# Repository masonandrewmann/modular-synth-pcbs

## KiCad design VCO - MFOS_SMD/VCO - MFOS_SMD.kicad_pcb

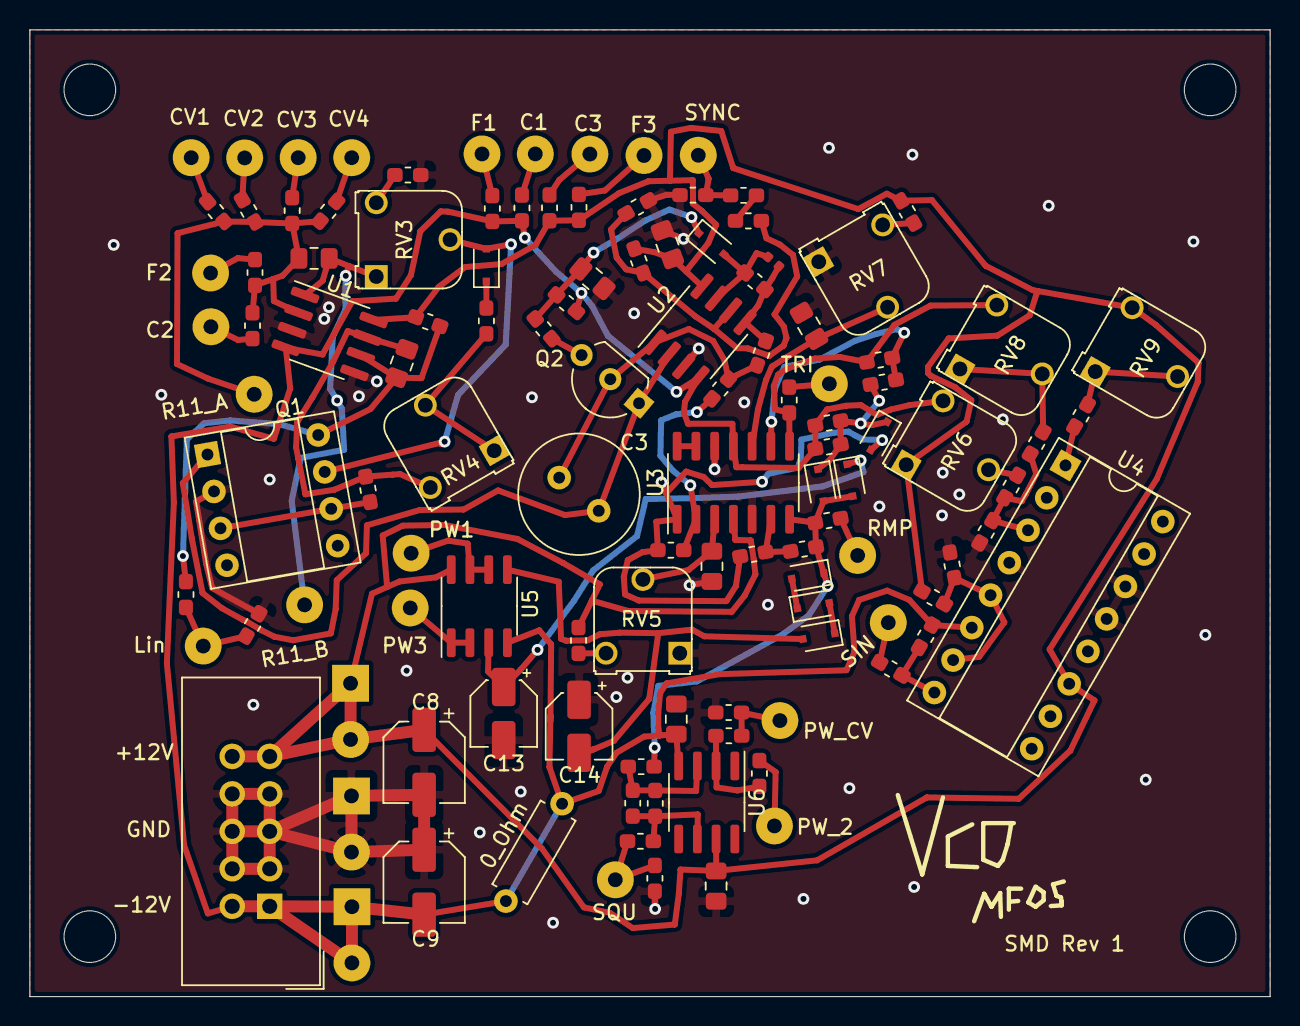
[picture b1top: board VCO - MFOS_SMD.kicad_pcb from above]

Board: 2 copper layers, 84.1 x 65.5 mm, 117 parts (0 on the bottom side), 66 nets.

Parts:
0_Ohm: R_Axial_DIN0207_L6.3mm_D2.5mm_P7.62mm_Horizontal
C1, C2, C5: 100pF; C_0805_2012Metric_Pad1.15x1.40mm_HandSolder
C3: 0.005uF; C_Radial_D8.0mm_H7.0mm_P3.50mm
C4: 0.001uF; C_0603_1608Metric_Pad1.05x0.95mm_HandSolder
C6: 4.7pF; C_0402_1005Metric
C7, C10, C11, C16, C17: 0.1uF; C_0805_2012Metric_Pad1.15x1.40mm_HandSolder
C8, C9: 10uF; CP_Elec_5x5.4
C12: 0.002uF; C_0603_1608Metric_Pad1.05x0.95mm_HandSolder
C13, C14: 1uF; CP_Elec_4x5.4
C15: 10pF; C_0603_1608Metric_Pad1.05x0.95mm_HandSolder
D1, D2, D3, D4, D5, D6, D7, D8: D; D_SOD-323F
J1: CV1; SolderWirePad_1x01_Drill1mm
J2: CV2; SolderWirePad_1x01_Drill1mm
J3: CV3; SolderWirePad_1x01_Drill1mm
J4: CV4; SolderWirePad_1x01_Drill1mm
J5: LIN; SolderWirePad_1x01_Drill1mm
J6: SYNC; SolderWirePad_1x01_Drill1mm
J7: RMP; SolderWirePad_1x01_Drill1mm
J8: TRI; SolderWirePad_1x01_Drill1mm
J9: SIN; SolderWirePad_1x01_Drill1mm
J10: PWM_CV; SolderWirePad_1x01_Drill1mm
J11: SQU; SolderWirePad_1x01_Drill1mm
J12: RV1P2; SolderWirePad_1x01_Drill1mm
J13: RV2P2; SolderWirePad_1x01_Drill1mm
J14: RV1P1; SolderWirePad_1x01_Drill1mm
J15: RV2P1; SolderWirePad_1x01_Drill1mm
J16: RV2P3; SolderWirePad_1x01_Drill1mm
J17: RV1P3; SolderWirePad_1x01_Drill1mm
J18: RV10P3; SolderWirePad_1x01_Drill1mm
J19: RV10P1; SolderWirePad_1x01_Drill1mm
J20: RV10P2; SolderWirePad_1x01_Drill1mm
J21: GND_CONN; SolderWirePad_1x02_P3.81mm_Drill1mm
J22: +12V_CONN; SolderWirePad_1x02_P3.81mm_Drill1mm
J23: -12V_CONN; SolderWirePad_1x02_P3.81mm_Drill1mm
J24: R11_inv; SolderWirePad_1x01_Drill1mm
J25: R11_out; SolderWirePad_1x01_Drill1mm
J26: Conn_01x10_Female; IDC-Header_2x05_P2.54mm_Vertical
Q1: SSM2210; DIP-8_W7.62mm_Socket
Q2: Q_PJFET_DSG; TO-92L_Inline_Wide
R1, R9: 200k; R_0603_1608Metric_Pad1.05x0.95mm_HandSolder
R2: 10k; R_0603_1608Metric_Pad1.05x0.95mm_HandSolder
R3, R14, R17, R25, R40: 1M; R_0603_1608Metric_Pad1.05x0.95mm_HandSolder
R4, R5, R6, R7, R8: 100k; R_0603_1608Metric_Pad1.05x0.95mm_HandSolder
R10: 47k; R_0603_1608Metric_Pad1.05x0.95mm_HandSolder
R12: 475; R_0603_1608Metric_Pad1.05x0.95mm_HandSolder
R13, R18, R20, R27, R38, R45, R46: 100K; R_0603_1608Metric_Pad1.05x0.95mm_HandSolder
R15, R44, R50: 4.7K; R_0603_1608Metric_Pad1.05x0.95mm_HandSolder
R16, R21, R23, R26, R29, R30, R35, R36, R47, R49: 10K; R_0603_1608Metric_Pad1.05x0.95mm_HandSolder
R19: 18k; R_0603_1608Metric_Pad1.05x0.95mm_HandSolder
R22, R32, R33, R41, R43: 1K; R_0603_1608Metric_Pad1.05x0.95mm_HandSolder
R24: 2K; R_0603_1608Metric_Pad1.05x0.95mm_HandSolder
R28: 47K; R_0603_1608Metric_Pad1.05x0.95mm_HandSolder
R31: 470K; R_0603_1608Metric_Pad1.05x0.95mm_HandSolder
R34, R39: 20K; R_0603_1608Metric_Pad1.05x0.95mm_HandSolder
R37: 20k; R_0603_1608Metric_Pad1.05x0.95mm_HandSolder
R42: 130K; R_0603_1608Metric_Pad1.05x0.95mm_HandSolder
R48: 10M; R_0603_1608Metric_Pad1.05x0.95mm_HandSolder
R51: 3K; R_0603_1608Metric_Pad1.05x0.95mm_HandSolder
RV3: 100; Potentiometer_Runtron_RM-065_Vertical
RV4, RV6, RV8: 100K; Potentiometer_Runtron_RM-065_Vertical
RV5, RV7: 10K; Potentiometer_Runtron_RM-065_Vertical
RV9: 1M; Potentiometer_Runtron_RM-065_Vertical
U1: OP275; SOIC-8_3.9x4.9mm_P1.27mm
U2, U5: TL072; SOIC-8_3.9x4.9mm_P1.27mm
U3: TL074; SOIC-14_3.9x8.7mm_P1.27mm
U4: LM13700; DIP-16_W7.62mm_Socket
U6: TL071; SOIC-8_3.9x4.9mm_P1.27mm

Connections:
+12V: C7.1, C8.1, C17.1, J22.1, J22.2, J26.9, J26.10, R9.1, R10.1, R17.1, R23.1, R27.2, R35.1, R40.1, RV6.1, RV9.3, U1.8, U2.8, U3.4, U4.11, U5.8, U6.7
-12V: 0_Ohm.1, 0_Ohm.2, C9.2, C12.2, C16.1, J23.1, J23.2, J26.1, J26.2, R1.2, R2.2, R19.2, R37.1, R44.1, RV6.3, U1.4, U2.4, U3.11, U4.6, U5.4, U6.4
Earth: C5.2, C7.2, C8.2, C9.1, C10.2, C11.2, C13.2, C14.1, C16.2, C17.2, J21.1, J21.2, J26.3, J26.4, J26.5, J26.6, J26.7, J26.8, Q1.2, R12.2, R13.1, R20.2, R24.1, R32.2, R42.1, R46.2, R51.2, RV5.1, RV7.1, U1.3, U1.5, U2.3, U3.5, U3.12, U4.4, U4.13, U4.14
unnamed: C1.1, J25.1, RV3.1, U1.1
unnamed: C1.2, J24.1, R3.1, R4.1, R5.1, R6.1, R7.1, R8.1, U1.2
unnamed: C2.1, Q1.8, R14.1, R17.2, U1.6
unnamed: C2.2, R16.1, RV4.3, U1.7
unnamed: C3.2, Q1.1, Q2.1, U2.2
unnamed: C4.1, J6.1, R20.1
unnamed: C4.2, R22.2
unnamed: C5.1, D2.1, R18.1, R19.1
unnamed: C6.1, R21.1, R25.2, U2.5
unnamed: C6.2, D2.2, R25.1, U2.7
unnamed: C10.1, RV5.2, U3.3
unnamed: C11.1, RV7.2, U3.10
unnamed: C12.1, D3.1, D4.1, R36.2, R37.2
unnamed: C13.1, D6.1, U5.3
unnamed: C14.2, D8.2, U5.5
unnamed: C15.1, R45.1, R48.2, U6.3
unnamed: C15.2, R48.1, R50.1, U6.6
unnamed: D1.1, R15.2
unnamed: D1.2, Q1.7, RV3.2
unnamed: D3.2, R28.1, R29.1, U3.1
unnamed: D4.2, D5.1, D6.2, R30.1, R33.2, R45.2, U3.7
unnamed: D5.2, D7.1
unnamed: D7.2, D8.1
unnamed: J1.1, R5.2
unnamed: J2.1, R6.2
unnamed: J3.1, R7.2
unnamed: J4.1, R8.2
unnamed: J5.1, R13.2, R14.2
unnamed: J7.1, R33.1
unnamed: J8.1, R41.1
unnamed: J9.1, R43.1
unnamed: J10.1, R46.1, R47.2
unnamed: J11.1, R50.2, R51.1
unnamed: J12.1, R4.2
unnamed: J13.1, R3.2
unnamed: J14.1, R2.1
unnamed: J15.1, R1.1
unnamed: J16.1, R9.2
unnamed: J17.1, R10.2
unnamed: J18.1, U5.1, U5.2
unnamed: J19.1, U5.6, U5.7
unnamed: J20.1, R49.1
unnamed: Q1.3, Q1.6, R16.2
unnamed: Q2.3, R18.2
unnamed: R12.1, RV3.3
unnamed: R15.1, RV4.1, RV4.2
unnamed: R22.1, R23.2, R24.2, U2.6
unnamed: R26.1, R28.2, U3.2
unnamed: R27.1, RV5.3
unnamed: R29.2, R30.2, U3.6
unnamed: R31.1, RV6.2
unnamed: R31.2, R32.1, R34.2, U4.3
unnamed: R34.1, RV8.1, RV8.2
unnamed: R35.2, RV7.3
unnamed: R36.1, R39.1, U3.9
unnamed: R38.1, RV9.1, RV9.2
unnamed: R38.2, U4.1
unnamed: R39.2, R41.2, RV8.3, U3.8
unnamed: R40.2, R42.2, U4.5, U4.7
unnamed: R43.2, R44.2, U4.8
unnamed: R47.1, R49.2, U6.2
unnamed: U3.13, U3.14
RAW: C3.1, Q2.2, R21.2, R26.2, U2.1

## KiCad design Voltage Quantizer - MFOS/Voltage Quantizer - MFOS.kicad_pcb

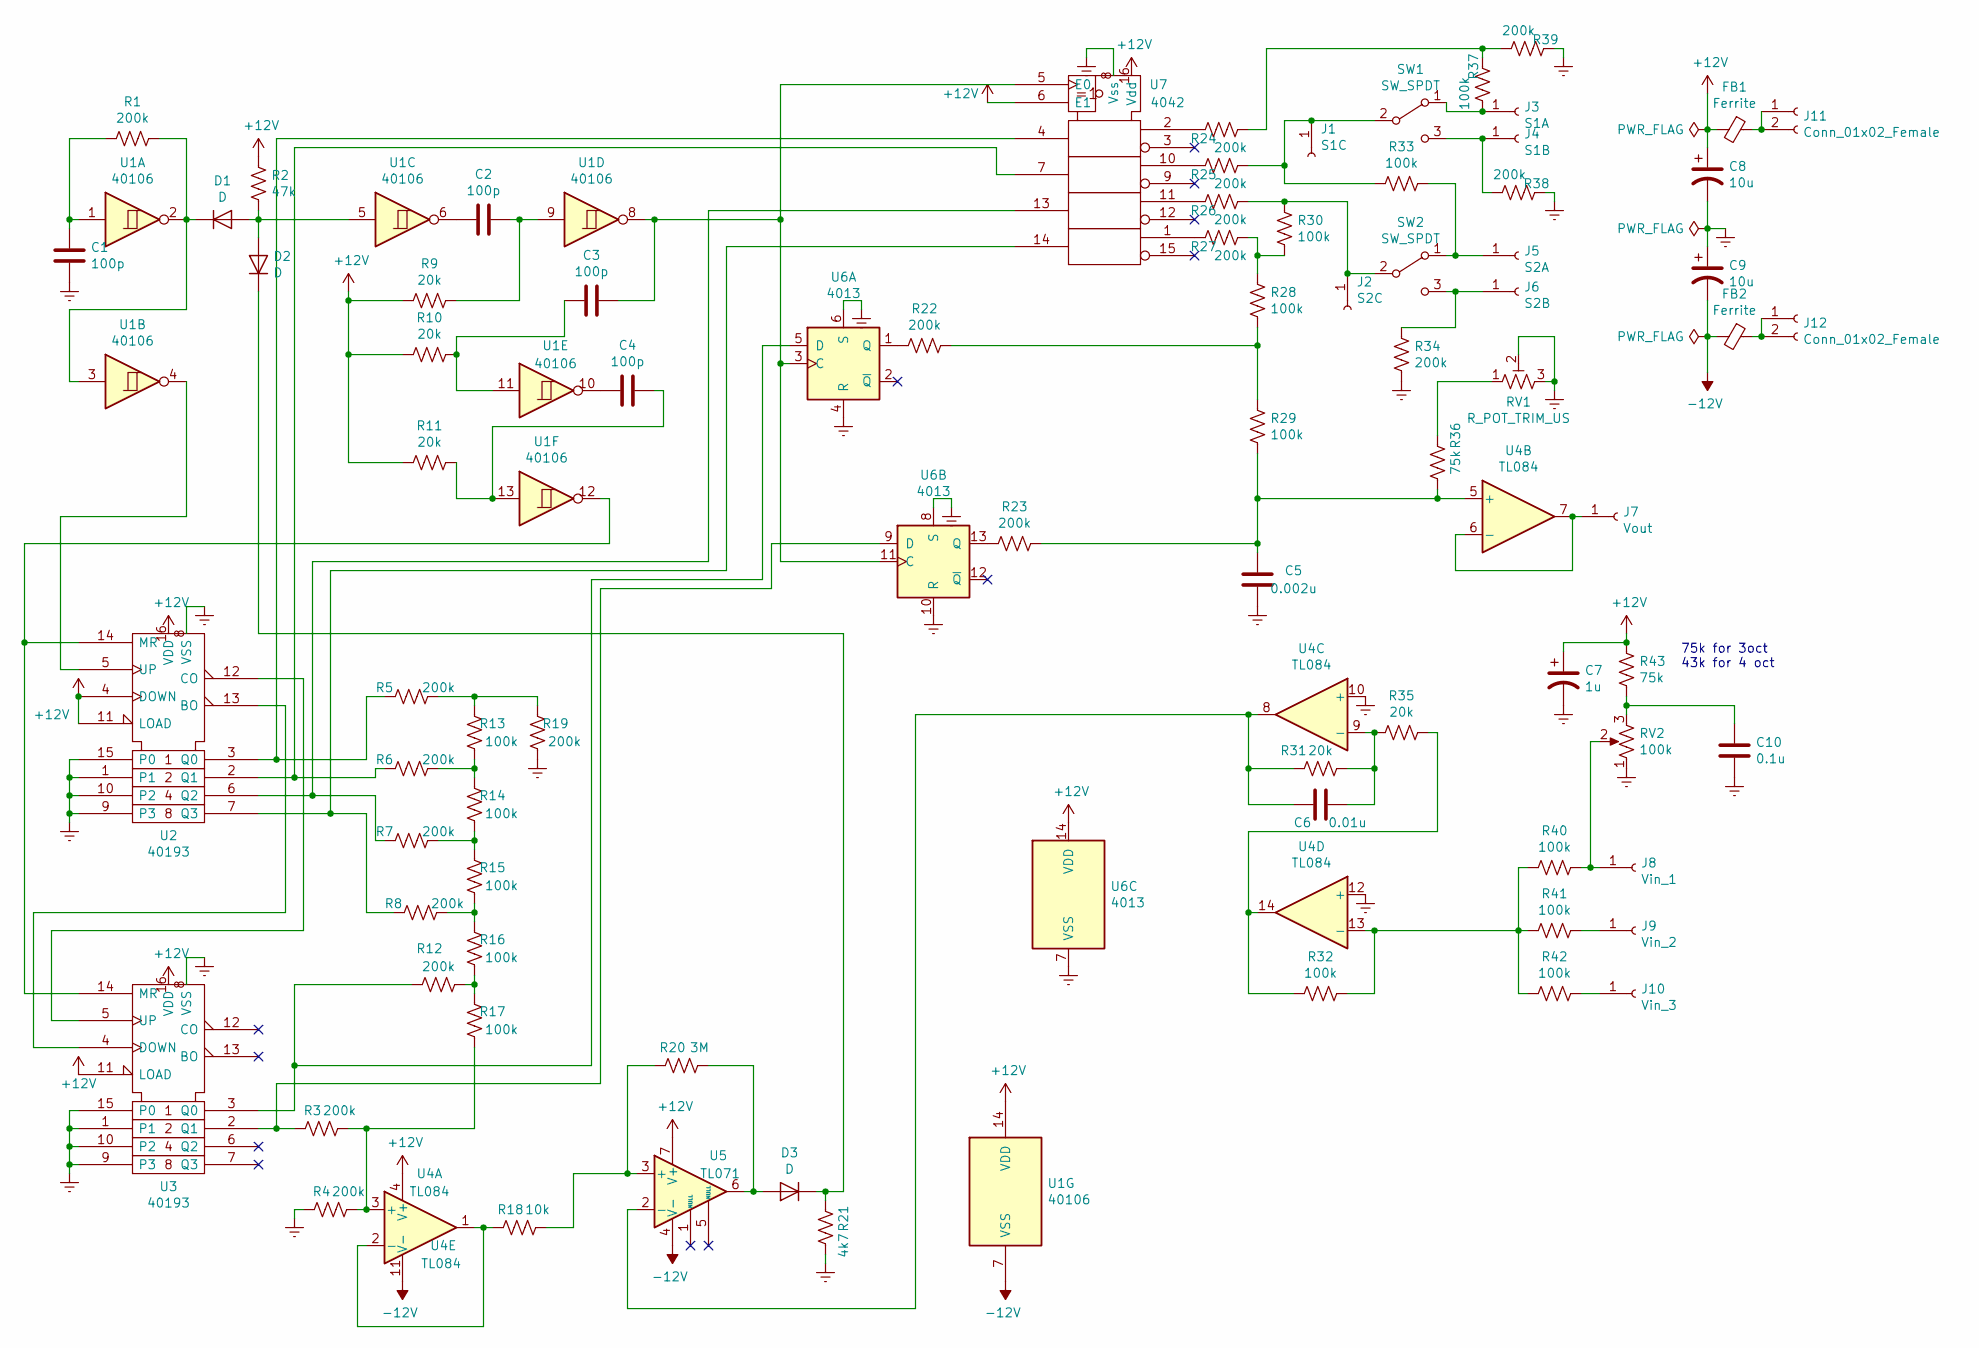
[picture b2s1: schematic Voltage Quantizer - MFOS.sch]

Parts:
C1, C2, C3, C4: 100p
C5: 0.002u
C6: 0.01u
C7: 1u
C8, C9: 10u
C10: 0.1u
D1, D2, D3: D
FB1, FB2: Ferrite
J1: S1C
J2: S2C
J3: S1A
J4: S1B
J5: S2A
J6: S2B
J7: Vout
J8: Vin_1
J9: Vin_2
J10: Vin_3
J11, J12: Conn_01x02_Female
R1, R3, R4, R5, R6, R7, R8, R12, R19, R22, R23, R24, R25, R26, R27, R34, R38, R39: 200k
R2: 47k
R9, R10, R11, R31, R35: 20k
R13, R14, R15, R16, R17, R28, R29, R30, R32, R33, R37, R40, R41, R42: 100k
R18: 10k
R20: 3M
R21: 4k7
R36, R43: 75k
RV1: R_POT_TRIM_US
RV2: 100k
SW1, SW2: SW_SPDT
U1: 40106
U2, U3: 40193
U4: TL084
U5: TL071
U6: 4013
U7: 4042

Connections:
+12V: C7.1, C8.1, FB1.2, R2.2, R9.1, R10.1, R11.1, R43.1, U1.14 (VDD), U2.4 (DOWN), U2.11 (LOAD), U2.16 (VDD), U3.11 (LOAD), U3.16 (VDD), U4.4 (V+), U5.7 (V+), U6.14 (VDD), U7.6 (E1), U7.16 (Vdd)
-12V: C9.2, FB2.2, U1.7 (VSS), U4.11 (V-), U5.4 (V-)
unnamed: C1.1, R1.2, U1.1
unnamed: C2.1, R9.2, U1.9
unnamed: C2.2, U1.6
unnamed: C3.1, U1.8, U6.3 (C), U6.11 (C), U7.5 (E0)
unnamed: C3.2, R10.2, U1.11
unnamed: C4.1, R11.2, U1.13
unnamed: C4.2, U1.10
unnamed: C5.2, R23.2, R29.2, R36.2, U4.5 (+)
unnamed: C6.1, R31.2, R35.1, U4.9 (-)
unnamed: C6.2, R31.1, U4.8, U5.2 (-)
unnamed 12: C10.1, R43.2, RV2.3; also elsewhere on the board
unnamed: D1.1 (K), R1.1, U1.2, U1.3
unnamed: D1.2 (A), D2.2 (A), R2.1, U1.5
unnamed: D2.1 (K), D3.1 (K), R21.1
unnamed: D3.2 (A), R20.2, U5.6
unnamed: FB1.1, J11.1, J11.2
unnamed: J1.1, R25.2, R33.2, SW1.2 (B)
unnamed: J2.1, R26.2, R30.1, SW2.2 (B)
unnamed: J3.1, R37.2, SW1.1 (A)
unnamed: J4.1, R38.2, SW1.3 (C)
unnamed: J5.1, R33.1, SW2.1 (A)
unnamed: J6.1, R34.2, SW2.3 (C)
unnamed: J7.1, U4.6 (-), U4.7
unnamed: J8.1, R40.2, RV2.2
unnamed: J9.1, R41.2
unnamed: J10.1, R42.2
unnamed: R3.1, U3.2 (Q1), U6.9 (D)
unnamed: R5.1, U2.3 (Q0), U7.4
unnamed: R6.1, U2.2 (Q1), U7.7
unnamed: R7.1, U2.6 (Q2), U7.13
unnamed: R8.1, U2.7 (Q3), U7.14
unnamed: R12.1, U3.3 (Q0), U6.5 (D)
unnamed: R12.2, R16.2, R17.1
unnamed: R5.2, R13.1, R19.1
unnamed: R6.2, R13.2, R14.1
unnamed: R7.2, R14.2, R15.1
unnamed: R8.2, R15.2, R16.1
unnamed: R3.2, R4.2, R17.2, U4.3 (+)
unnamed: R18.1, U4.1, U4.2 (-)
unnamed: R18.2, R20.1, U5.3 (+)
unnamed: R22.1, U6.1 (Q)
unnamed: R22.2, R28.2, R29.1
unnamed: R23.1, U6.13 (Q)
unnamed: R24.1, U7.2
unnamed: R24.2, R37.1, R39.2
unnamed: R25.1, U7.10
unnamed: R26.1, U7.11
unnamed: R27.1, U7.1
unnamed: R27.2, R28.1, R30.2
unnamed: R32.1, R35.2, U4.14
unnamed: R32.2, R40.1, R41.1, R42.1, U4.13 (-)
unnamed: R36.1, RV1.1
unnamed: U1.4, U2.5 (UP)
unnamed: U1.12, U2.14 (MR), U3.14 (MR)
unnamed: U2.12 (CO), U3.5 (UP)
unnamed: U2.13 (BO), U3.4 (DOWN)

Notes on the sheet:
75k for 3oct 43k for 4 oct

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
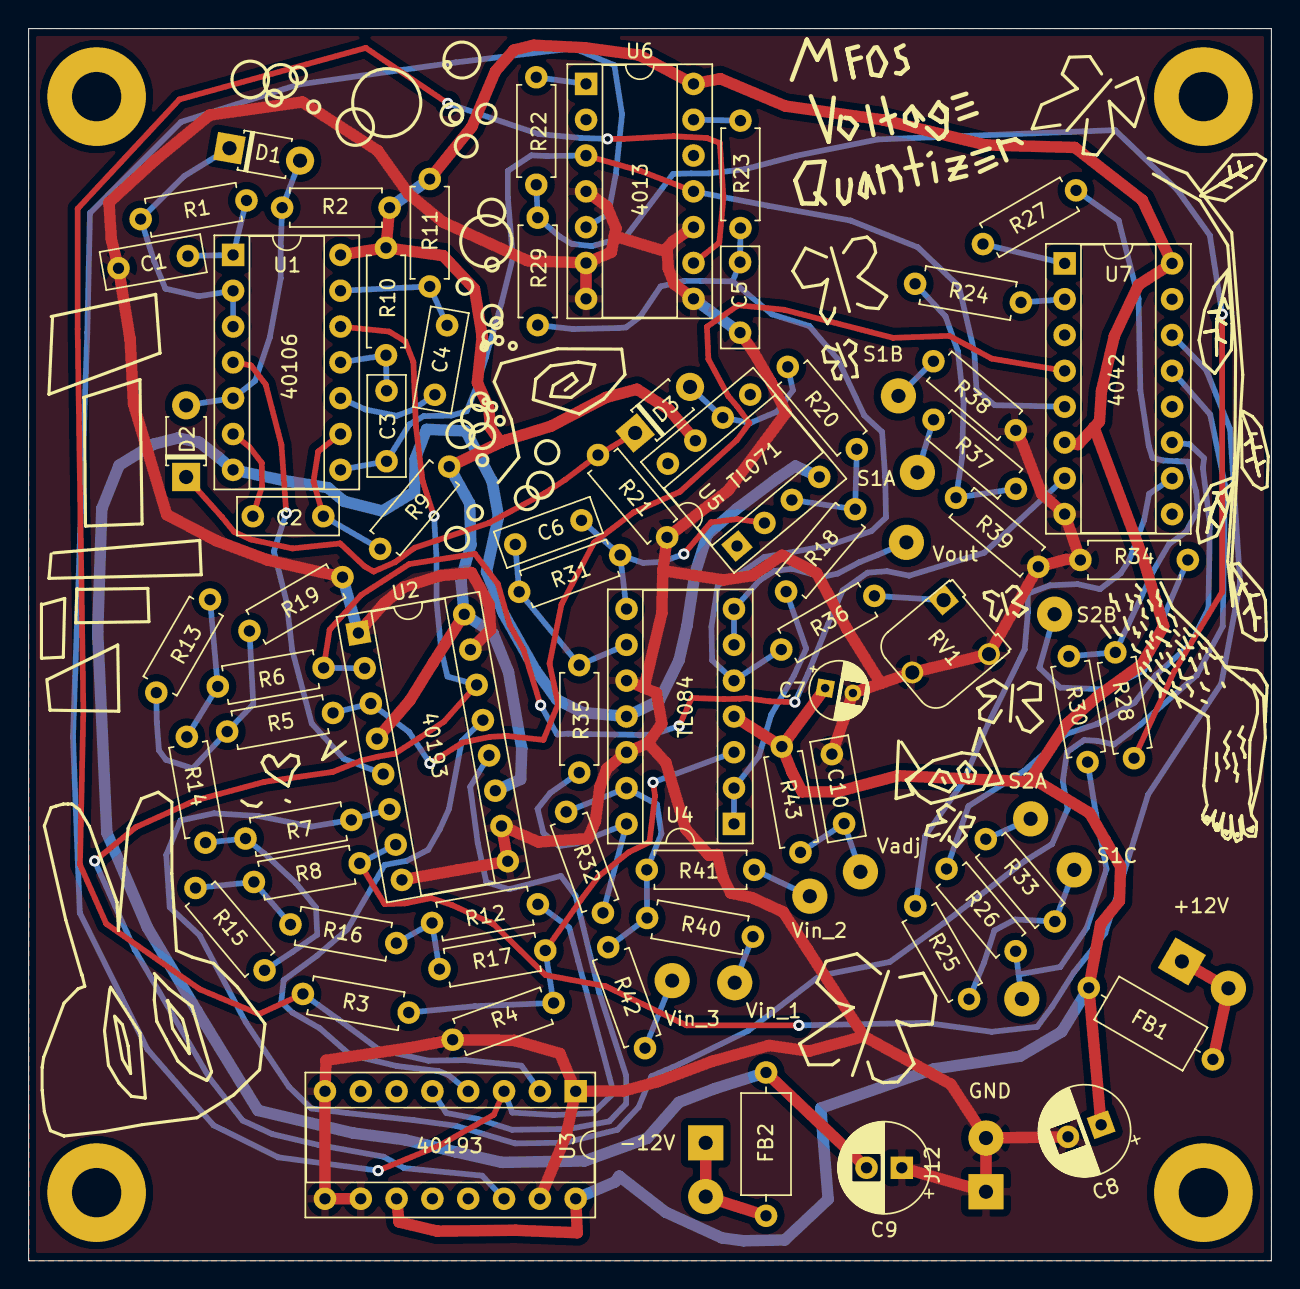
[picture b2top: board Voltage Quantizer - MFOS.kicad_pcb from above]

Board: 2 copper layers, 88.1 x 87.4 mm, 80 parts (0 on the bottom side), 60 nets.

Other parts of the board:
J13: -12V; SolderWirePad_1x02_P3.81mm_Drill1mm
J14: Vadj; SolderWirePad_1x01_Drill1mm

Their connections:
unnamed 12: J14.1; also elsewhere on the board

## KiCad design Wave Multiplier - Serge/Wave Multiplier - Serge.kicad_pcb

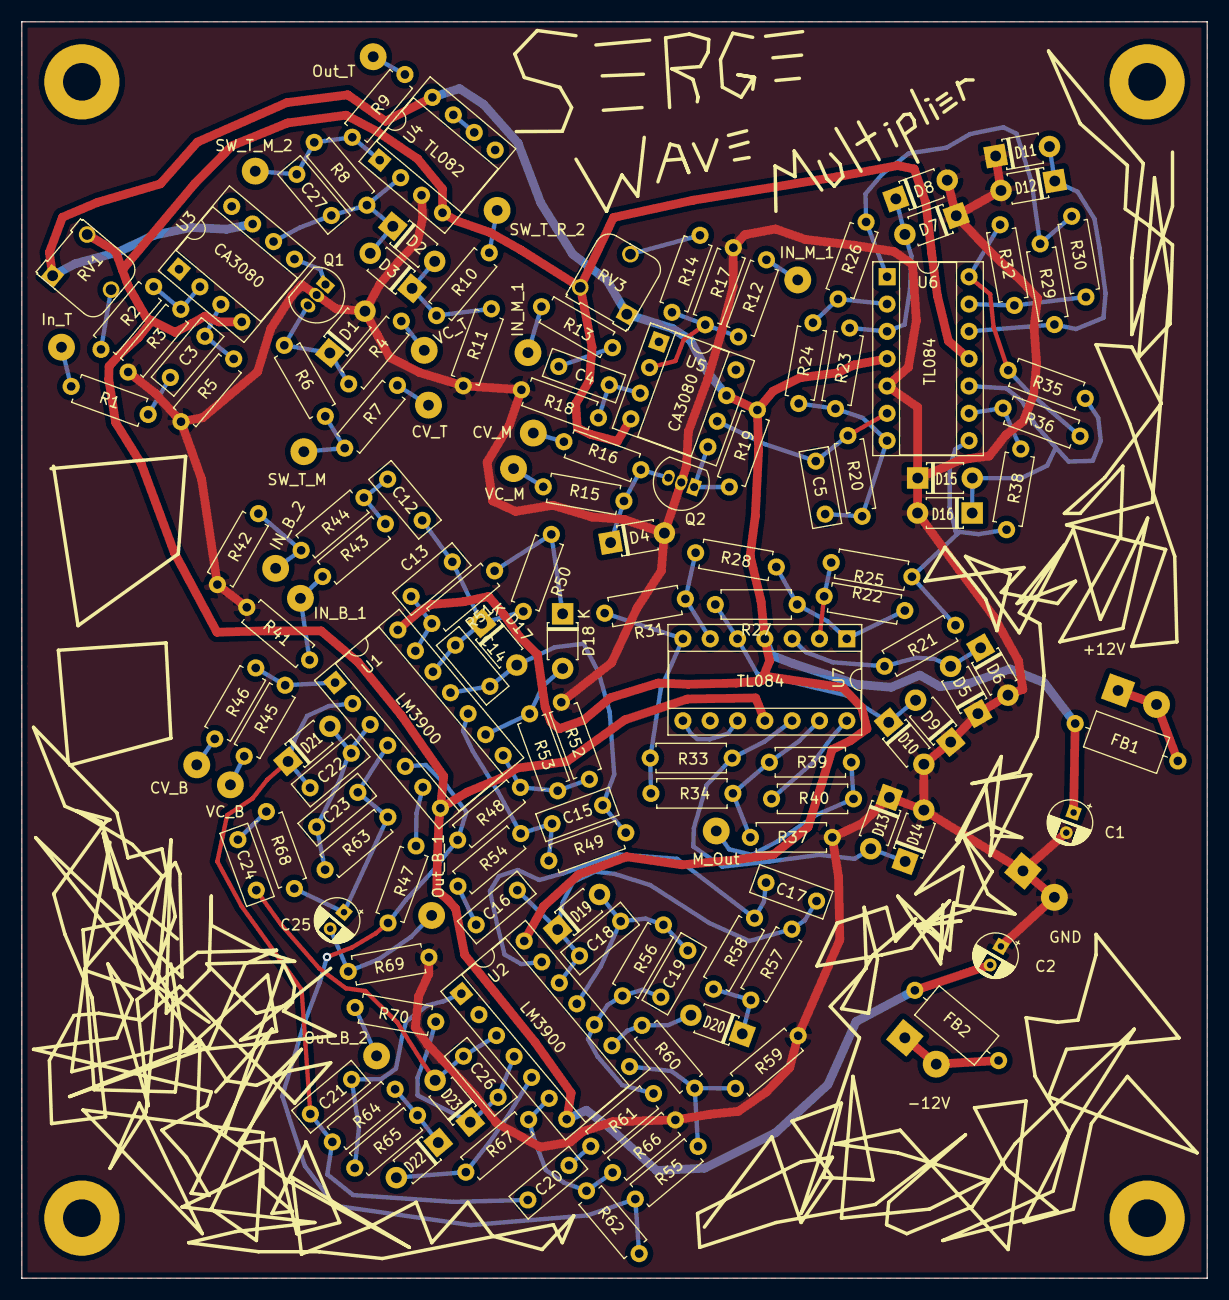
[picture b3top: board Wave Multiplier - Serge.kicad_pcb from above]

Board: 2 copper layers, 110.2 x 116.8 mm, 148 parts (0 on the bottom side), 89 nets.

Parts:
C1, C2: 10u; CP_Radial_D4.0mm_P2.00mm
C3, C4: 220n; C_Rect_L7.0mm_W2.5mm_P5.00mm
C5: 150p; C_Rect_L7.0mm_W2.5mm_P5.00mm
C12, C16, C20, C24: 47n; C_Rect_L7.0mm_W2.5mm_P5.00mm
C13, C17, C21: 1u; C_Rect_L7.0mm_W2.5mm_P5.00mm
C14, C18, C22, C27: 47p; C_Rect_L7.0mm_W2.5mm_P5.00mm
C15, C19, C23, C26: 30p; C_Rect_L7.0mm_W2.5mm_P5.00mm
C25: 47u; CP_Radial_D4.0mm_P2.00mm
D1, D2, D3, D4, D5, D6, D7, D8, D9, D10, D11, D12, D13, D14, D15, D16, D17, D18, D19, D20, D21, D22: D; D_T-1_P5.08mm_Horizontal
D23: 4v3; D_T-1_P5.08mm_Horizontal
FB1, FB2: Ferrite; L_Axial_L7.0mm_D3.3mm_P10.16mm_Horizontal_Fastron_MICC
J1: In_T; SolderWirePad_1x01_Drill1mm
J2: CV; SolderWirePad_1x01_Drill1mm
J3: +12V_Conn; SolderWirePad_1x02_P3.81mm_Drill1mm
J4: GND_Conn; SolderWirePad_1x02_P3.81mm_Drill1mm
J5: -12V_Conn; SolderWirePad_1x02_P3.81mm_Drill1mm
J6: VC_T; SolderWirePad_1x01_Drill1mm
J7: SW_T_M; SolderWirePad_1x01_Drill1mm
J8: SW_T_M_2; SolderWirePad_1x01_Drill1mm
J9: Out_T; SolderWirePad_1x01_Drill1mm
J10: SW_T_R_2; SolderWirePad_1x01_Drill1mm
J11: CV_M; SolderWirePad_1x01_Drill1mm
J12, J13: IN_M_1; SolderWirePad_1x01_Drill1mm
J14: VC_M; SolderWirePad_1x01_Drill1mm
J15: M_Out; SolderWirePad_1x01_Drill1mm
J16: CV_B; SolderWirePad_1x01_Drill1mm
J17: In_B_1; SolderWirePad_1x01_Drill1mm
J18: In_B_2; SolderWirePad_1x01_Drill1mm
J19: VC_B; SolderWirePad_1x01_Drill1mm
J20: Out_B_1; SolderWirePad_1x01_Drill1mm
J21: Out_B_2; SolderWirePad_1x01_Drill1mm
Q1, Q2: BC557; TO-92_Inline
R1, R12, R13, R22, R24, R25, R26, R28, R30, R31, R32, R34, R36, R38, R39, R41, R42, R46, R68, R69: 100k; R_Axial_DIN0207_L6.3mm_D2.5mm_P7.62mm_Horizontal
R2, R14: 3M3; R_Axial_DIN0207_L6.3mm_D2.5mm_P7.62mm_Horizontal
R3, R5, R17, R18: 1k5; R_Axial_DIN0207_L6.3mm_D2.5mm_P7.62mm_Horizontal
R4, R7, R8, R55: 330k; R_Axial_DIN0207_L6.3mm_D2.5mm_P7.62mm_Horizontal
R6: 22k; R_Axial_DIN0207_L6.3mm_D2.5mm_P7.62mm_Horizontal
R9, R70: 1k; R_Axial_DIN0207_L6.3mm_D2.5mm_P7.62mm_Horizontal
R10, R37: 10k; R_Axial_DIN0207_L6.3mm_D2.5mm_P7.62mm_Horizontal
R11: 3k3; R_Axial_DIN0207_L6.3mm_D2.5mm_P7.62mm_Horizontal
R15: 47k; R_Axial_DIN0207_L6.3mm_D2.5mm_P7.62mm_Horizontal
R16: 15k; R_Axial_DIN0207_L6.3mm_D2.5mm_P7.62mm_Horizontal
R19: 6M8; R_Axial_DIN0207_L6.3mm_D2.5mm_P7.62mm_Horizontal
R20: 82k; R_Axial_DIN0207_L6.3mm_D2.5mm_P7.62mm_Horizontal
R21, R23, R27, R29, R33, R35: 33k; R_Axial_DIN0207_L6.3mm_D2.5mm_P7.62mm_Horizontal
R40: 330; R_Axial_DIN0207_L6.3mm_D2.5mm_P7.62mm_Horizontal
R43, R44, R53, R54, R61: 1M; R_Axial_DIN0207_L6.3mm_D2.5mm_P7.62mm_Horizontal
R45, R48: 220k; R_Axial_DIN0207_L6.3mm_D2.5mm_P7.62mm_Horizontal
R47: 150k; R_Axial_DIN0207_L6.3mm_D2.5mm_P7.62mm_Horizontal
R49, R56, R63, R67: 2M2; R_Axial_DIN0207_L6.3mm_D2.5mm_P7.62mm_Horizontal
R50, R51, R57, R58, R64, R65: 10M; R_Axial_DIN0207_L6.3mm_D2.5mm_P7.62mm_Horizontal
R52, R59, R66: 820k; R_Axial_DIN0207_L6.3mm_D2.5mm_P7.62mm_Horizontal
R60: 1M5; R_Axial_DIN0207_L6.3mm_D2.5mm_P7.62mm_Horizontal
R62: 470k; R_Axial_DIN0207_L6.3mm_D2.5mm_P7.62mm_Horizontal
RV1, RV3: 100k; Potentiometer_Runtron_RM-065_Vertical
U1, U2: LM3900; DIP-14_W7.62mm_Socket
U3, U5: CA3080; DIP-8_W7.62mm_Socket
U4: TL082; DIP-8_W7.62mm_Socket
U6, U7: TL084; DIP-14_W7.62mm_Socket

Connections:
+12V: C1.1, FB1.2, R19.1, RV1.1, RV3.1, U1.14, U2.14, U3.7, U4.8, U5.7, U6.4, U7.4
-12V: C2.2, FB2.2, RV1.3, RV3.3, U1.7, U2.7, U3.4, U4.4, U5.4, U6.11, U7.11
Earth: C1.2, C2.1, D1.2, D4.2, D5.1, D6.2, D7.1, D8.2, D9.1, D10.2, D11.1, D12.2, D13.1, D14.2, D15.1, D16.2, J4.1, J4.2, Q1.2, Q2.2, R3.2, R5.1, R11.1, R17.2, R18.2, R37.2, R41.1, R42.1, R52.1, R59.1, R66.1, R69.1, U4.3, U6.5
unnamed: C3.1, R5.2, U3.3
unnamed: C3.2, R1.1
unnamed: C4.1, R18.1, U5.3
unnamed: C4.2, R13.2
unnamed: C5.1, R20.2, R23.1, R24.1, U6.7
unnamed: C5.2, R20.1, U5.6, U6.6
unnamed: C12.1, C13.2, C14.1, D17.1, R50.2, U1.12
unnamed: C12.2, R43.1, R44.1
unnamed: C13.1, R51.2, U1.13
unnamed: C14.2, C15.2, D17.2, R49.2, U1.11
unnamed: C15.1, R49.1, R54.2, U1.10
unnamed: C16.1, R54.1
unnamed: C16.2, C17.2, C18.1, D19.1, R57.2, U2.12
unnamed: C17.1, R58.2, U2.13
unnamed: C18.2, C19.2, D19.2, R56.2, U2.11
unnamed: C19.1, R56.1, R61.2, U2.10
unnamed: C20.1, R61.1
unnamed: C20.2, C21.2, C22.1, D21.1, R64.2, U1.2
unnamed: C21.1, R65.2, U2.1
unnamed: C22.2, C23.2, D21.2, R63.2, U1.3
unnamed: C23.1, C25.1, R63.1, R68.2, U1.4
unnamed: C24.1, R68.1
unnamed: C24.2, C26.1, D23.2, U2.3
unnamed: C25.2, J20.1, R69.2
unnamed: C26.2, D23.1, R70.1, U2.4
unnamed: C27.1, J8.1, R8.1, R9.2, U4.1
unnamed: C27.2, D2.1, D3.2, R8.2, U3.6, U4.2
unnamed: D1.1, Q1.3, R4.1, R6.2
unnamed: D2.2, D3.1, R10.1, R11.2
unnamed: D4.1, Q2.3, R15.2, R16.2
unnamed: D5.2, D6.1, R21.2, U7.3
unnamed: D7.2, D8.1, R23.2, U6.3
unnamed: D9.2, D10.1, R27.2, U7.5
unnamed: D11.2, D12.1, R29.2, U6.12
unnamed: D13.2, D14.1, R33.2, U7.12
unnamed: D15.2, D16.1, R35.2, U6.10
unnamed: D18.1, R50.1, R51.1
unnamed: D18.2, R53.1, U1.9
unnamed: D20.1, R57.1, R58.1
unnamed: D20.2, R60.1, U2.9
unnamed: D22.1, R64.1, R65.1
unnamed: D22.2, R67.1, U2.5
unnamed: FB1.1, J3.1, J3.2
unnamed: FB2.1, J5.1, J5.2
unnamed: J1.1, R1.2
unnamed: J2.1, R7.2
unnamed: J6.1, R4.2
unnamed: J7.1, R6.1, R7.1
unnamed: J9.1, R9.1
unnamed: J10.1, R10.2
unnamed: J11.1, R16.1
unnamed: J12.1, R12.1
unnamed: J13.1, R13.1
unnamed: J14.1, R15.1
unnamed: J15.1, R39.2, R40.2
unnamed: J16.1, R46.2
unnamed: J17.1, R41.2, R43.2
unnamed: J18.1, R42.2, R44.2
unnamed: J19.1, R45.2
unnamed: J21.1, R70.2
unnamed: Q1.1, U3.5
unnamed: Q2.1, R19.2, U5.5
unnamed: R2.1, R3.1, U3.2
unnamed: R2.2, RV1.2
unnamed: R12.2, R14.2, R17.1, U5.2
unnamed: R14.1, RV3.2
unnamed: R21.1, R22.1, R38.2, U6.8
unnamed: R22.2, R25.1, U7.2
unnamed: R24.2, R26.1, U6.2
unnamed: R25.2, R27.1, R28.2, U7.1
unnamed: R26.2, R29.1, R30.2, U6.1
unnamed: R28.1, R31.1, U7.6
unnamed: R30.1, R32.1, U6.13
unnamed: R31.2, R33.1, R34.1, U7.7
unnamed: R32.2, R35.1, R36.1, U6.14
unnamed: R34.2, R37.1, R39.1, U7.13
unnamed: R36.2, R38.1, U6.9
unnamed: R40.1, U7.14
unnamed: R45.1, R46.1, U1.1
unnamed: R47.1, R48.1, R55.1, R62.1, U1.5
unnamed: R47.2, U1.6
unnamed: R48.2, R52.2, R53.2, U1.8
unnamed: R55.2, R59.2, R60.2, U2.8
unnamed: R62.2, R66.2, R67.2, U2.6
unnamed: U4.6, U4.7
unnamed: U7.8, U7.10

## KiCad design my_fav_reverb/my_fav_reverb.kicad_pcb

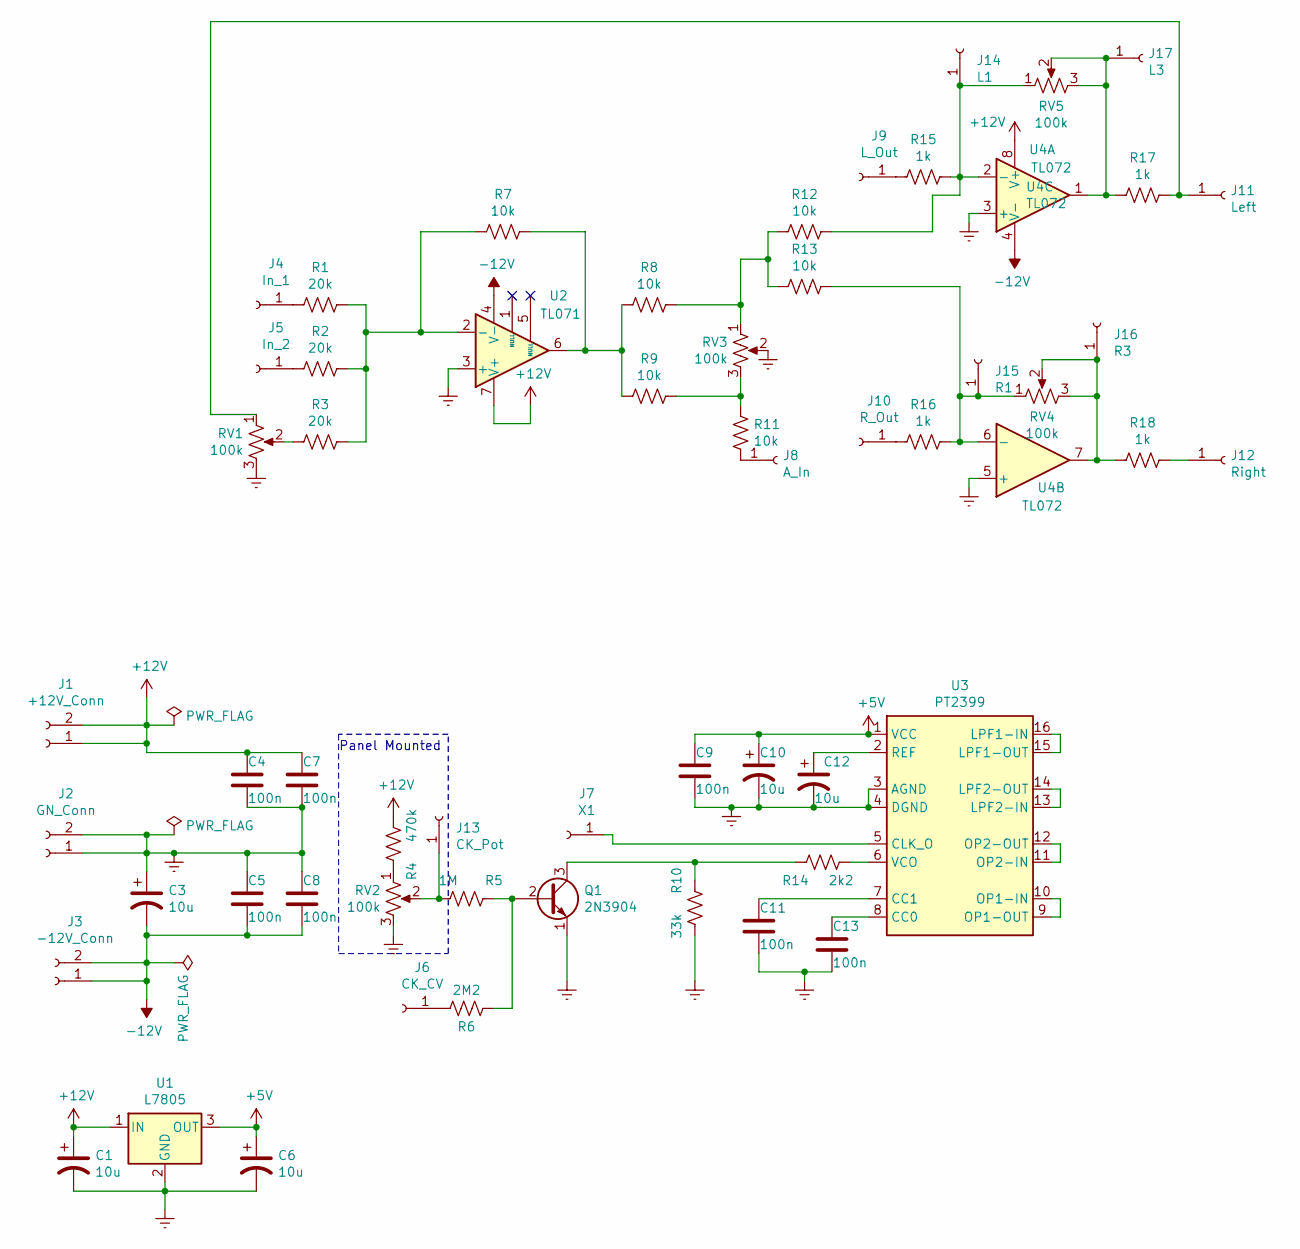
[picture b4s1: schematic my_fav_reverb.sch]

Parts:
C1, C3, C6, C10, C12: 10u; CP_Radial_D5.0mm_P2.0mm_Bigger_Holes
C4, C5, C7, C8, C9, C11, C13: 100n; C_Rect_L7.0mm_W2.5mm_P5.00mm
J1: +12V_Conn; SolderWirePad_1x02_P3.81mm_Drill1.2mm
J2: GN_Conn; SolderWirePad_1x02_P3.81mm_Drill1.2mm
J3: -12V_Conn; SolderWirePad_1x02_P3.81mm_Drill1.2mm
J4: In_1; SolderWirePad_1x01_Drill1mm
J5: In_2; SolderWirePad_1x01_Drill1mm
J6: CK_CV; SolderWirePad_1x01_Drill1mm
J7: X1; SolderWirePad_1x01_Drill1mm
J8: A_In; SolderWirePad_1x01_Drill1mm
J9: L_Out; SolderWirePad_1x01_Drill1mm
J10: R_Out; SolderWirePad_1x01_Drill1mm
J11: Left; SolderWirePad_1x01_Drill1mm
J12: Right; SolderWirePad_1x01_Drill1mm
J13: CK_Pot; SolderWirePad_1x01_Drill1mm
J14: L1; SolderWirePad_1x01_Drill1mm
J15: R1; SolderWirePad_1x01_Drill1mm
J16: R3; SolderWirePad_1x01_Drill1mm
J17: L3; SolderWirePad_1x01_Drill1mm
Q1: 2N3904; TO-92_Wide
R1, R2, R3: 20k; R_Axial_DIN0207_L6.3mm_D2.5mm_P7.62mm_Horizontal
R4: 470k; R_Axial_DIN0207_L6.3mm_D2.5mm_P7.62mm_Horizontal
R5: 1M; R_Axial_DIN0207_L6.3mm_D2.5mm_P7.62mm_Horizontal
R6: 2M2; R_Axial_DIN0207_L6.3mm_D2.5mm_P7.62mm_Horizontal
R7, R8, R9, R11, R12, R13: 10k; R_Axial_DIN0207_L6.3mm_D2.5mm_P7.62mm_Horizontal
R10: 33k; R_Axial_DIN0207_L6.3mm_D2.5mm_P7.62mm_Horizontal
R14: 2k2; R_Axial_DIN0207_L6.3mm_D2.5mm_P7.62mm_Horizontal
R15, R16, R17, R18: 1k; R_Axial_DIN0207_L6.3mm_D2.5mm_P7.62mm_Horizontal
RV1, RV3: 100k; Potentiometer_Alps_RK097_Single_Horizontal_NoClearance
RV2, RV4, RV5: 100k; BatteryHolder_Keystone_1060_1x2032
U1: L7805; TO-220-3_Vertical
U2: TL071; DIP-8_W7.62mm_Socket
U3: PT2399; DIP-16_W7.62mm_Socket
U4: TL072; DIP-8_W7.62mm_Socket

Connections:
+5V: C6.1, C9.1, C10.1, U1.3 (OUT), U3.1 (VCC)
+12V: C1.1, C4.1, C7.1, J1.1, J1.2, R4.1, U1.1 (IN), U2.7 (V+), U4.8 (V+)
-12V: C3.2, C5.2, C8.2, J3.1, J3.2, U2.4 (V-), U4.4 (V-)
Earth: C1.2, C3.1, C4.2, C5.1, C6.2, C7.2, C8.1, C9.2, C10.2, C11.2, C12.2, C13.2, J2.1, J2.2, Q1.1 (E), R10.1, RV1.3, RV2.3, RV3.2, U1.2 (GND), U2.3 (+), U3.3 (AGND), U3.4 (DGND), U4.3 (+), U4.5 (+)
unnamed: C11.1, U3.7 (CC1)
unnamed: C12.1, U3.2 (REF)
unnamed: C13.1, U3.8 (CC0)
unnamed: J4.1, R1.2
unnamed: J5.1, R2.2
unnamed: J6.1, R6.1
unnamed: J7.1, U3.5 (CLK_O)
unnamed: J8.1, R11.1
unnamed: J9.1, R15.2
unnamed: J10.1, R16.2
unnamed: J11.1, R17.1, RV1.1
unnamed: J12.1, R18.1
unnamed: J13.1, R5.1, RV2.2
unnamed: J14.1, R12.1, R15.1, RV5.1, U4.2 (-)
unnamed: J15.1, R13.1, R16.1, RV4.1, U4.6 (-)
unnamed: J16.1, R18.2, RV4.2, RV4.3, U4.7
unnamed: J17.1, R17.2, RV5.2, RV5.3, U4.1
unnamed: Q1.2 (B), R5.2, R6.2
unnamed: Q1.3 (C), R10.2, R14.2
unnamed: R1.1, R2.1, R3.1, R7.2, U2.2 (-)
unnamed: R3.2, RV1.2
unnamed: R4.2, RV2.1
unnamed: R7.1, R8.2, R9.2, U2.6
unnamed: R9.1, R11.2, RV3.3
unnamed: R8.1, R12.2, R13.2, RV3.1
unnamed: R14.1, U3.6 (VCO)
unnamed: U3.9 (OP1-OUT), U3.10 (OP1-IN)
unnamed: U3.11 (OP2-IN), U3.12 (OP2-OUT)
unnamed: U3.13 (LPF2-IN), U3.14 (LPF2-OUT)
unnamed: U3.15 (LPF1-OUT), U3.16 (LPF1-IN)

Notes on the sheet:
Panel Mounted

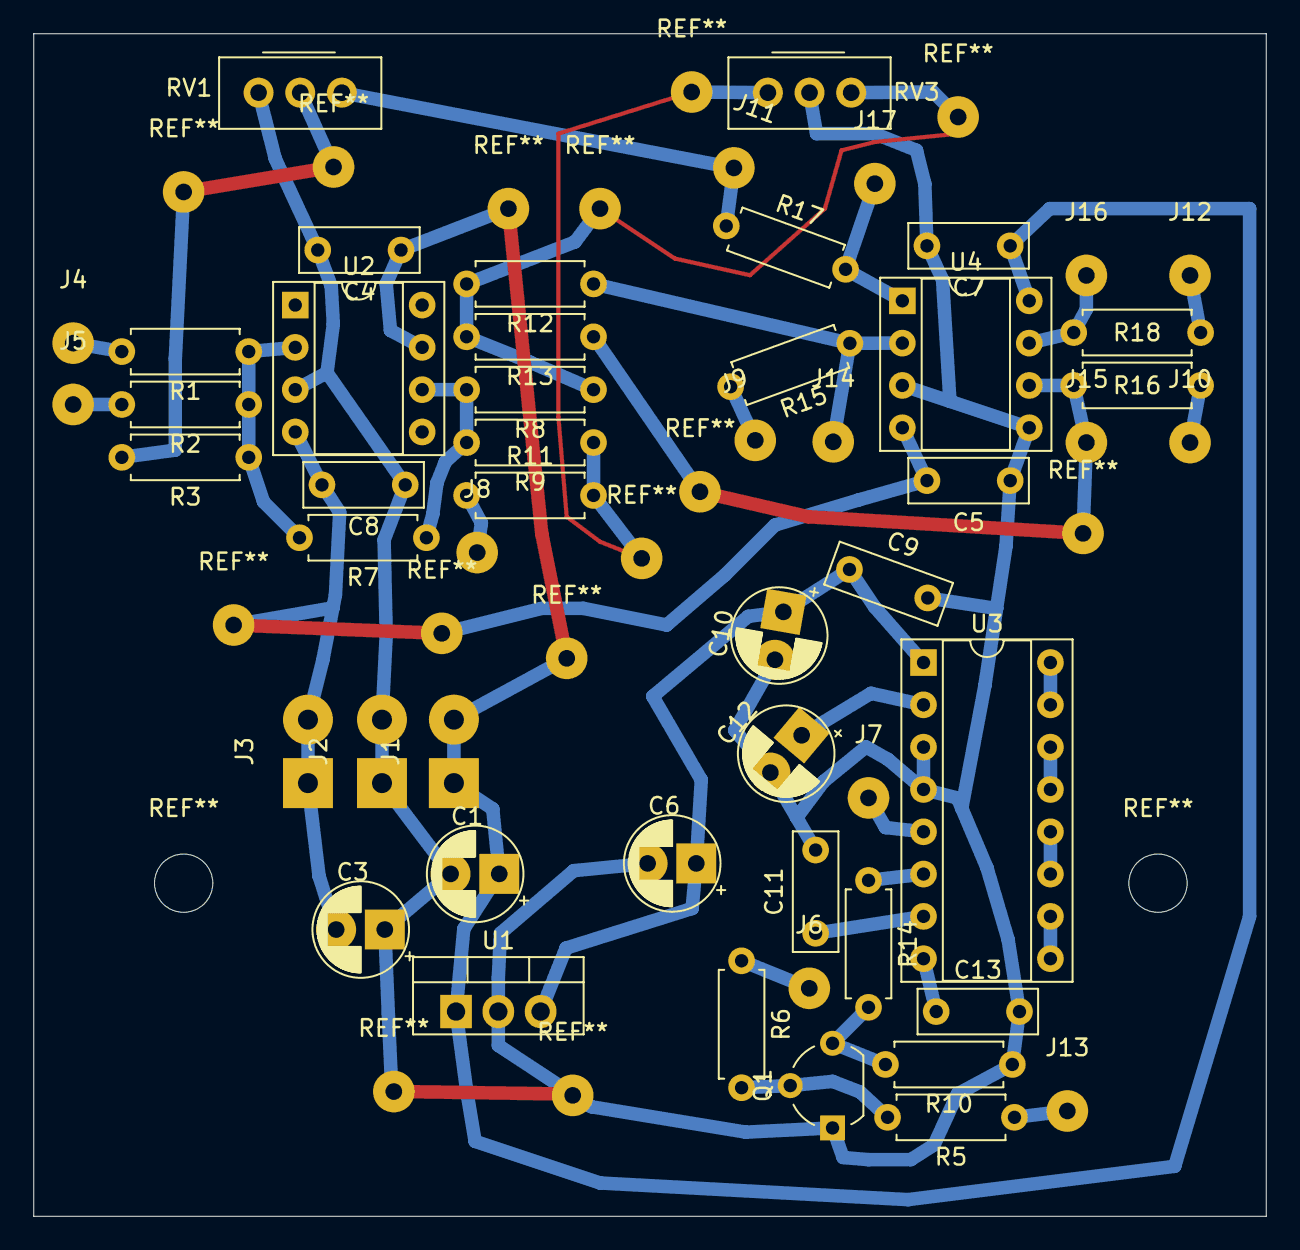
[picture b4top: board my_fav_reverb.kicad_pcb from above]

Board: 2 copper layers, 74.0 x 71.0 mm, 53 parts (0 on the bottom side), 33 nets.
